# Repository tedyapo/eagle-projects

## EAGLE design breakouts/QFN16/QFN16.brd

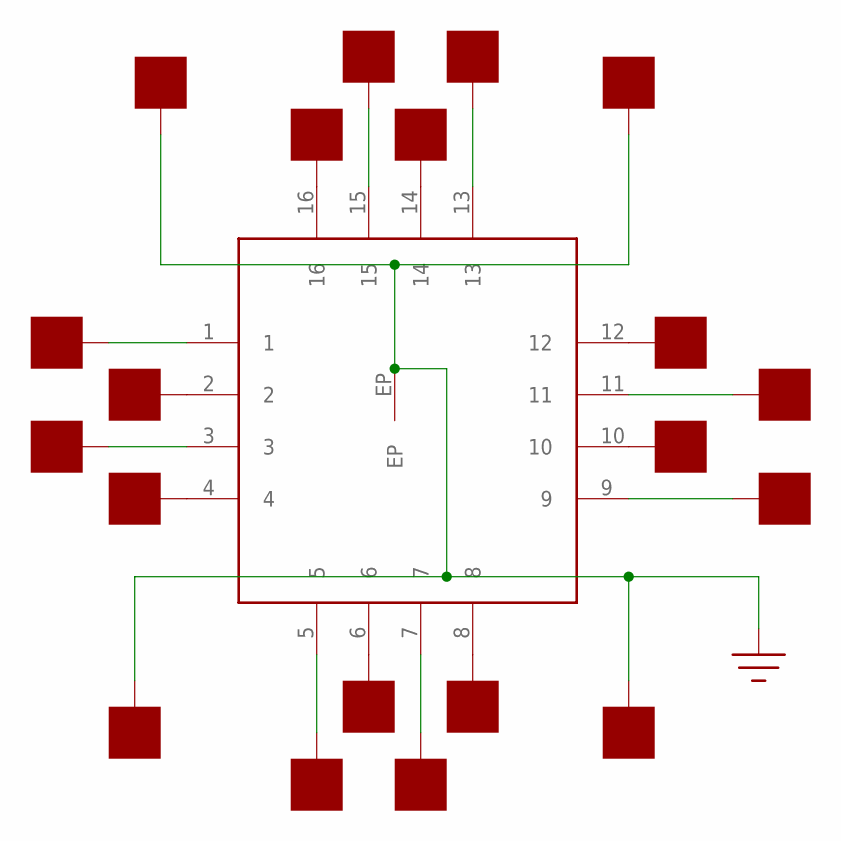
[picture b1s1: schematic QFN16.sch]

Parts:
U$1: QFN16; TQFN16-EP
U$2, U$3, U$4, U$5, U$6, U$7, U$8, U$9, U$10, U$11, U$12, U$13, U$14, U$15, U$16, U$17, U$18, U$19, U$20, U$21: PAD50MIL; PAD_50MIL

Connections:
GND: U$1.EP, U$18.P$1, U$19.P$1, U$20.P$1, U$21.P$1
unnamed: U$1.12, U$2.P$1
unnamed: U$1.10, U$4.P$1
unnamed: U$1.8, U$6.P$1
unnamed: U$1.6, U$8.P$1
unnamed: U$1.4, U$10.P$1
unnamed: U$1.2, U$12.P$1
unnamed: U$1.16, U$14.P$1
unnamed: U$1.14, U$16.P$1
unnamed: U$1.15, U$15.P$1
unnamed: U$1.13, U$17.P$1
unnamed: U$1.11, U$3.P$1
unnamed: U$1.9, U$5.P$1
unnamed: U$1.7, U$7.P$1
unnamed: U$1.5, U$9.P$1
unnamed: U$1.3, U$11.P$1
unnamed: U$1.1, U$13.P$1

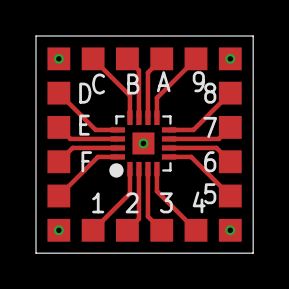
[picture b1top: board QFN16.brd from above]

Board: 2 copper layers, 12.1 x 12.1 mm, 21 parts (0 on the bottom side), 17 nets.

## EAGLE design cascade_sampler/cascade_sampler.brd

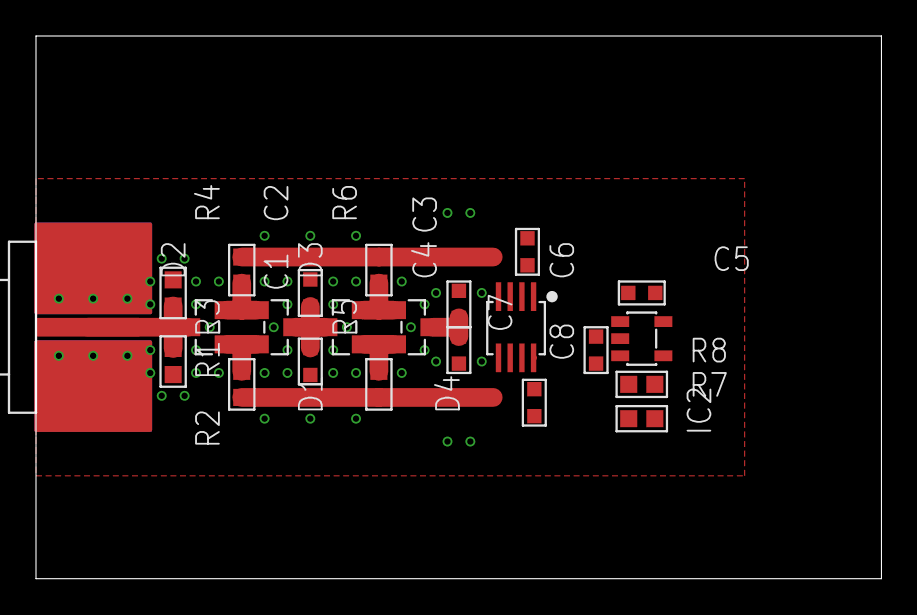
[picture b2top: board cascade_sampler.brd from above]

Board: 4 copper layers, 47.0 x 30.1 mm, 23 parts (0 on the bottom side), 14 nets.

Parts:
C1, C2, C3, C4, C5, C6, C7, C8: C0603
D1, D2, D3, D4: SOT-23
IC1: SSOP8
IC2: SOT23-5
J1: EDGE_LAUNCH_RF_CON_NARROW
R1, R2, R3, R4, R5, R6, R7, R8: R0603

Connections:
+2.5V: C5.P$2, C7.P$2, IC1.1, IC1.8, IC2.5
-2.5V: C6.P$2, C8.P$2, IC1.2, IC1.4, IC1.7, IC2.2
GND: C1.P$1, C2.P$2, C3.P$2, C4.P$1, C5.P$1, C6.P$1, C7.P$1, C8.P$1, J1.GND@1, J1.GND@2, J1.GND@3, J1.GND@4, J1.GND@5, J1.GND@6, J1.SHIELD@1, J1.SHIELD@2, R1.P$1, R2.P$2, R7.P$2
unnamed: D2.3, J1.CENTER, R1.P$2, R2.P$1
unnamed: C1.P$2, C2.P$1, D1.3, D3.3
unnamed: D1.2, D2.1, R3.P$2
unnamed: D1.1, D2.2, R4.P$1
unnamed: C3.P$1, C4.P$2, D4.3, IC2.1
unnamed: D3.1, D4.2, R5.P$2
unnamed: D3.2, D4.1, R6.P$1
unnamed: IC2.3, R7.P$1, R8.P$1
unnamed: IC2.4, R8.P$2
S+: IC1.5, R3.P$1, R5.P$1
S-: IC1.3, R4.P$2, R6.P$2

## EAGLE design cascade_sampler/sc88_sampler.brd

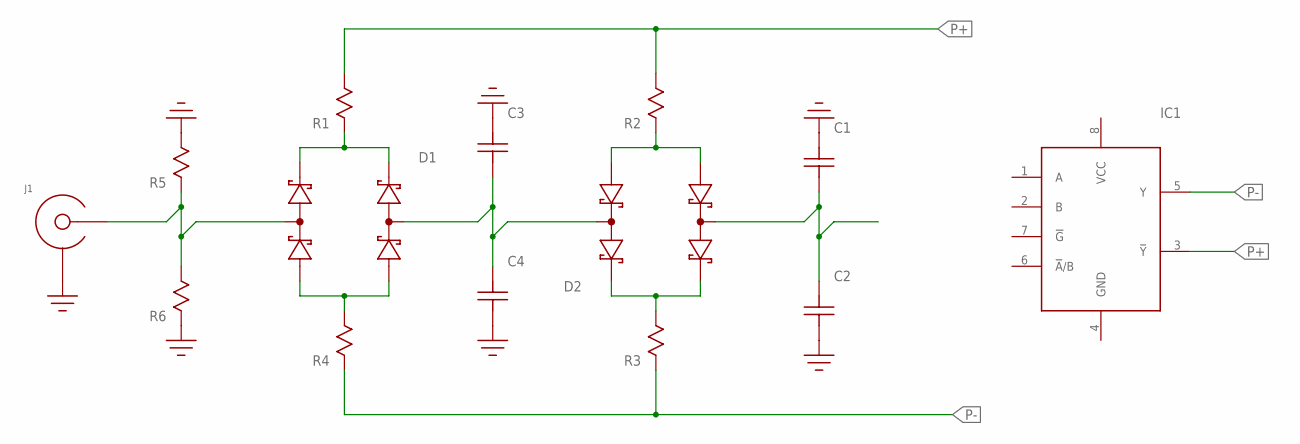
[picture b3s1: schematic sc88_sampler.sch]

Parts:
C1, C2, C3, C4: C; C0402
D1, D2: SMS3923-081; SC-88
IC1: 74LVC2G157; SSOP8
J1: EDGE_LAUNCH_JACK; EDGE_LAUNCH_RF_CON
R1, R2, R3, R4, R5, R6: R0402; 0402

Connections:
GND: C1.2, C2.1, C3.2, C4.1, J1.GND@1 (SHIELD), J1.GND@2 (SHIELD), J1.GND@3 (SHIELD), J1.GND@4 (SHIELD), J1.GND@5 (SHIELD), J1.GND@6 (SHIELD), J1.GND@7 (SHIELD), J1.GND@8 (SHIELD), J1.GND@9 (SHIELD), J1.GND@10 (SHIELD), J1.GND@11 (SHIELD), J1.GND@12 (SHIELD), J1.SHIELD@1 (SHIELD), J1.SHIELD@2 (SHIELD), R5.2, R6.1
unnamed: D1.5 (COMMON1), J1.CENTER, R5.1, R6.2
unnamed: D1.1 (ANODE0), D1.6 (ANODE1), R4.2
unnamed: D1.3 (CATHODE0), D1.4 (CATHODE1), R1.1
unnamed: C1.1, C2.2, D2.5 (COMMON1)
unnamed: D2.1 (ANODE0), D2.6 (ANODE1), R2.1
unnamed: D2.3 (CATHODE0), D2.4 (CATHODE1), R3.2
unnamed: C3.1, C4.2, D1.2 (COMMON0), D2.2 (COMMON0)
P+: IC1.3 (!Y!), R1.2, R2.2
P-: IC1.5 (Y), R3.1, R4.1

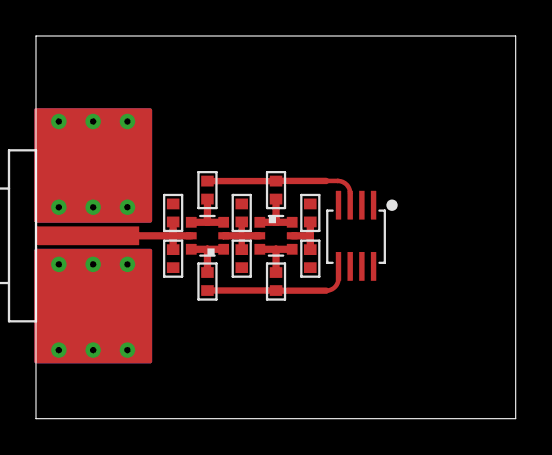
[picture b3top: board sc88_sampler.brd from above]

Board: 2 copper layers, 26.6 x 21.3 mm, 14 parts (0 on the bottom side), 10 nets.

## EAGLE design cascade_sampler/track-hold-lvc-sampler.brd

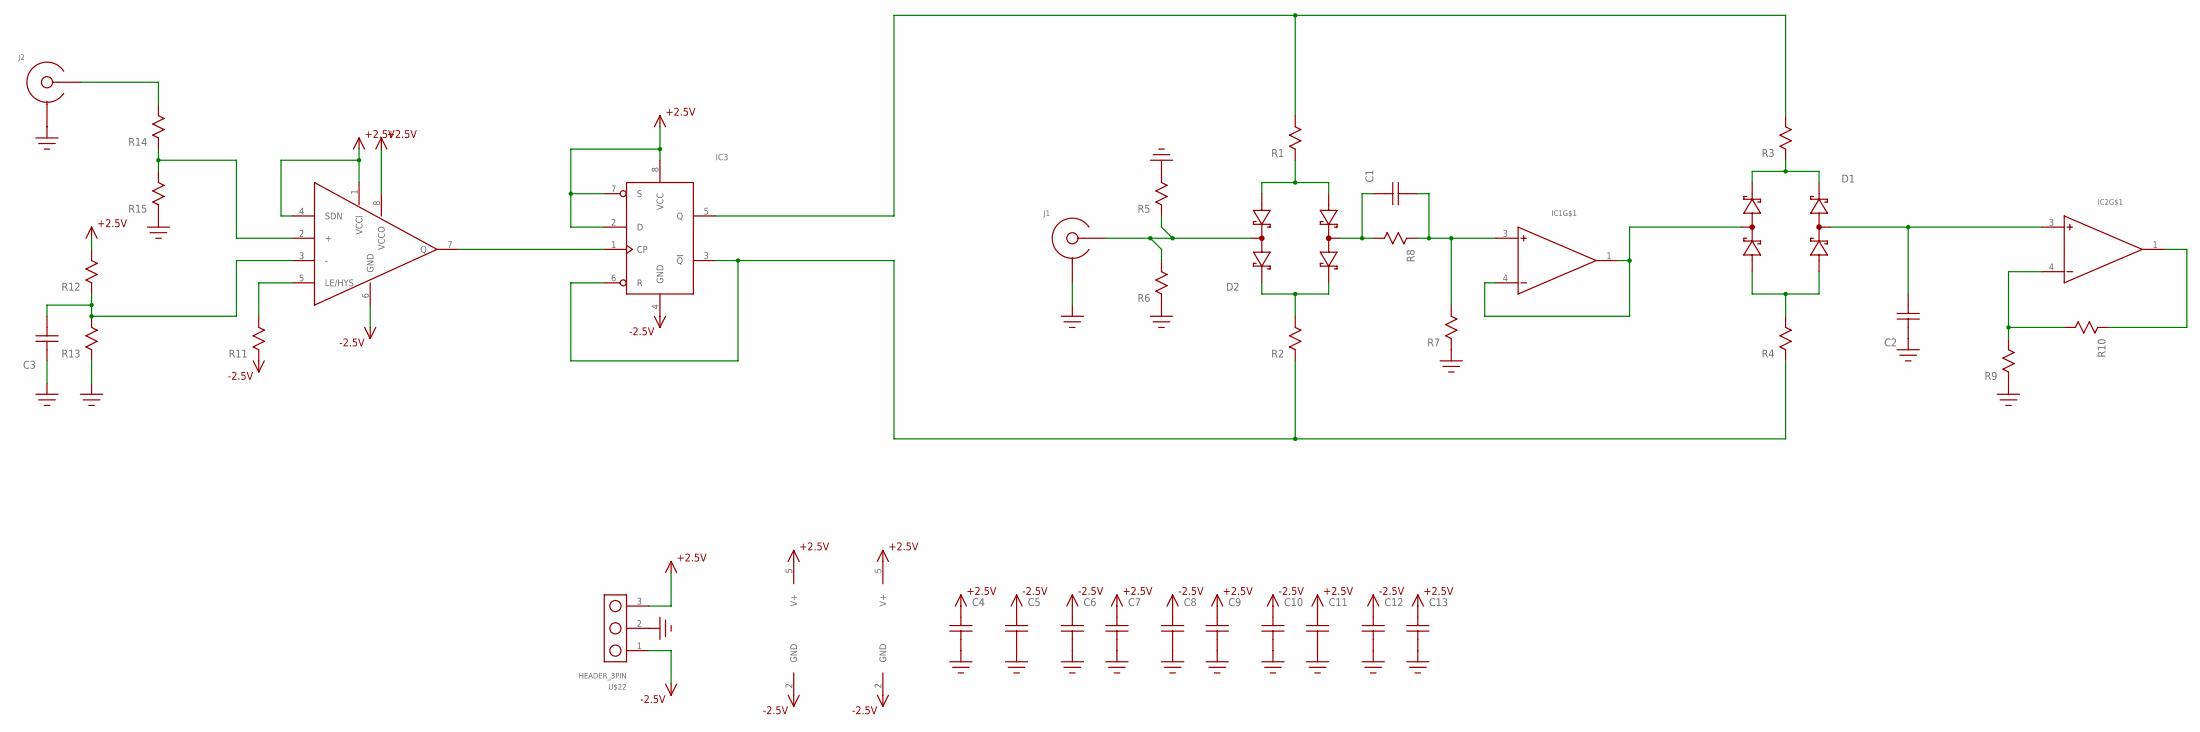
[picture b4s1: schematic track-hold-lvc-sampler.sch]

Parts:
C1, C2, C3, C6, C7, C8, C9, C10, C11, C12, C13: C0603
C4, C5: C1206; 1206
D1, D2: SMS3923-081; SC-88
IC1, IC2: ADA4000TSOT; TSOT-23
IC3: 74LVC2G74; SSOP8
IC4: ADCMP602; MSOP8
J1, J2: SMA-EDGE-LAUNCH4L-4020-TAPER-FIXED; SMA_EDGE_LAUNCH_4L_4020_TAPER_FIXED
R1, R2, R3, R4, R7, R8, R9, R10, R11, R12, R13, R14, R15: R0603
R5, R6: R0402; 0402
U$22: HEADER_3PIN

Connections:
+2.5V: C4.P$2, C7.P$2, C9.P$2, C11.P$2, C13.P$2, IC1.5 (V+), IC2.5 (V+), IC3.2 (D), IC3.7 (S), IC3.8 (VCC), IC4.1 (VCCI), IC4.4 (SDN), IC4.8 (VCCO), R12.P$2, U$22.3
-2.5V: C5.P$2, C6.P$2, C8.P$2, C10.P$2, C12.P$2, IC1.2 (GND), IC2.2 (GND), IC3.4 (GND), IC4.6 (GND), R11.P$1, U$22.1
GND: C2.P$2, C3.P$2, C4.P$1, C5.P$1, C6.P$1, C7.P$1, C8.P$1, C9.P$1, C10.P$1, C11.P$1, C12.P$1, C13.P$1, J1.BOTTOM_GND (SHIELD), J1.GND@1 (SHIELD), J1.GND@2 (SHIELD), J1.GND@3 (SHIELD), J1.GND@4 (SHIELD), J1.GND@5 (SHIELD), J1.GND@6 (SHIELD), J1.GND@7 (SHIELD), J1.GND@8 (SHIELD), J1.GND@14 (SHIELD), J1.GND@15 (SHIELD), J1.GND@16 (SHIELD), J1.GND@17 (SHIELD), J1.GND_PAD1 (SHIELD), J1.GND_PAD2 (SHIELD), J1.P$1 (SHIELD), J1.P$2 (SHIELD), J2.BOTTOM_GND (SHIELD), J2.GND@1 (SHIELD), J2.GND@2 (SHIELD), J2.GND@3 (SHIELD), J2.GND@4 (SHIELD), J2.GND@5 (SHIELD), J2.GND@6 (SHIELD), J2.GND@7 (SHIELD), J2.GND@8 (SHIELD), J2.GND@14 (SHIELD), J2.GND@15 (SHIELD), J2.GND@16 (SHIELD), J2.GND@17 (SHIELD), J2.GND_PAD1 (SHIELD), J2.GND_PAD2 (SHIELD), J2.P$1 (SHIELD), J2.P$2 (SHIELD), R5.2, R6.1, R7.P$1, R9.P$1, R13.P$1, R15.P$1, U$22.2
unnamed: D2.2 (COMMON0), J1.CENTER@1 (CENTER), J1.P$3 (CENTER), R5.1, R6.2
unnamed: D2.1 (ANODE0), D2.6 (ANODE1), R1.P$1
unnamed: D2.3 (CATHODE0), D2.4 (CATHODE1), R2.P$2
unnamed: D1.3 (CATHODE0), D1.4 (CATHODE1), R3.P$1
unnamed: D1.1 (ANODE0), D1.6 (ANODE1), R4.P$2
unnamed: D1.5 (COMMON1), IC1.1 (OUT), IC1.4 (-)
unnamed: C1.P$2, D2.5 (COMMON1), R8.P$2
unnamed: C1.P$1, IC1.3 (+), R7.P$2, R8.P$1
unnamed: IC3.3 (!Q!), IC3.6 (R), R2.P$1, R4.P$1
unnamed: IC3.1 (CP), IC4.7 (Q)
unnamed: C2.P$1, D1.2 (COMMON0), IC2.3 (+)
unnamed: IC2.4 (-), R9.P$2, R10.P$2
unnamed: IC2.1 (OUT), R10.P$1
unnamed: IC4.5 (LE/HYS), R11.P$2
unnamed: IC3.5 (Q), R1.P$2, R3.P$2
unnamed: C3.P$1, IC4.3 (-), R12.P$1, R13.P$2
unnamed: J2.CENTER@1 (CENTER), J2.P$3 (CENTER), R14.P$2
unnamed: IC4.2 (+), R14.P$1, R15.P$2

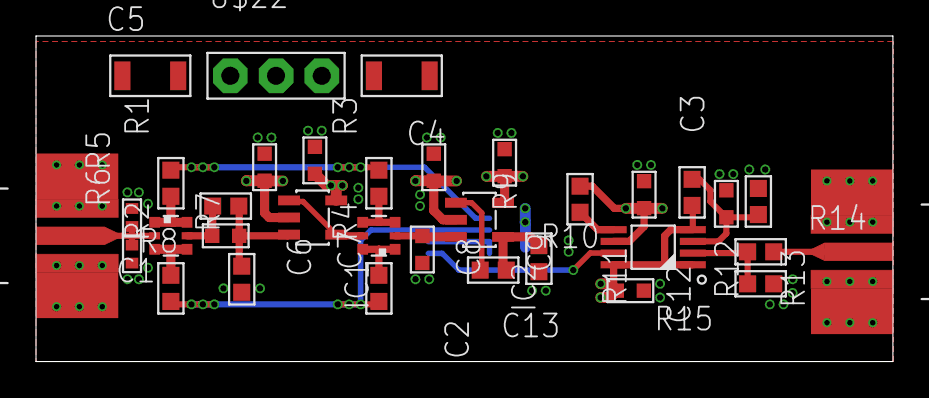
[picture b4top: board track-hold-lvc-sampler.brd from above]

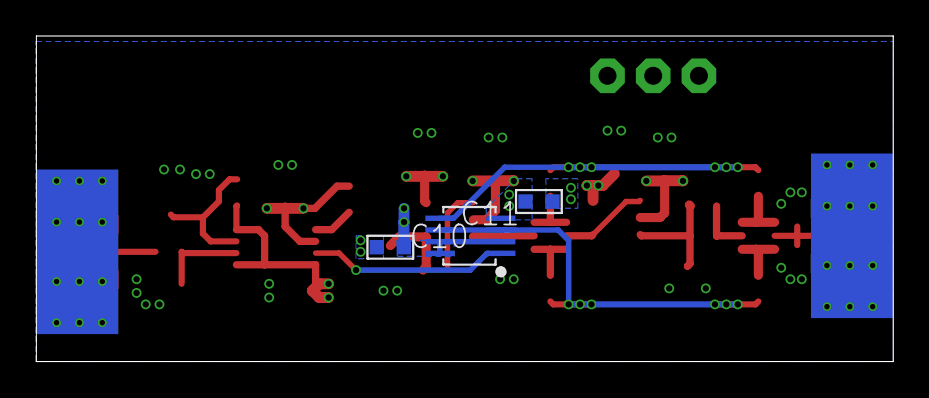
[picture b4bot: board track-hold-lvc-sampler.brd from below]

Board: 4 copper layers, 47.6 x 18.1 mm, 37 parts (3 on the bottom side), 21 nets.

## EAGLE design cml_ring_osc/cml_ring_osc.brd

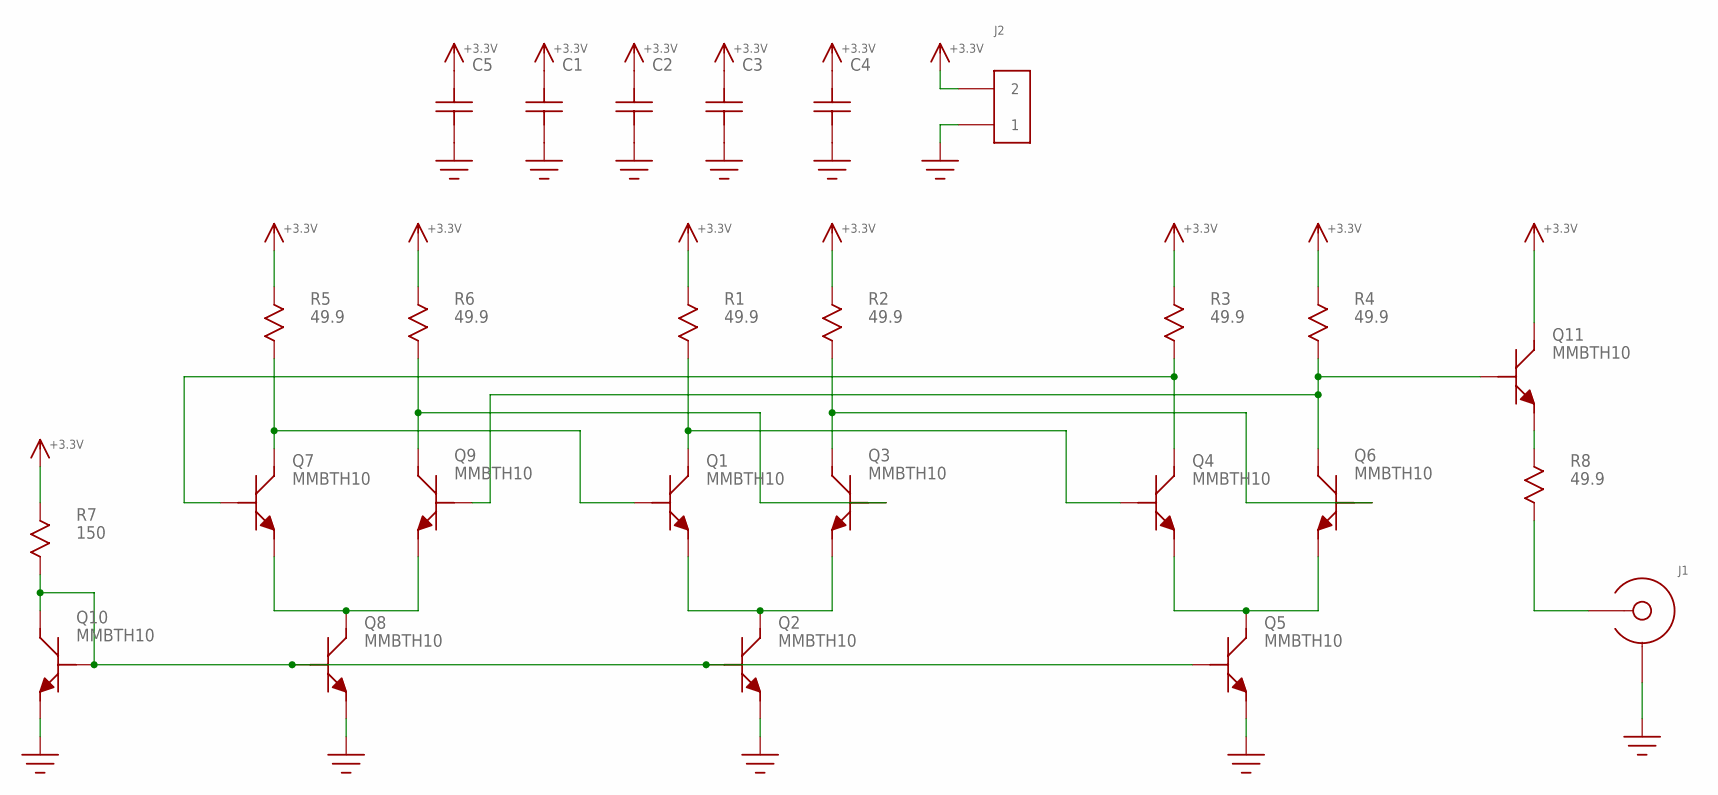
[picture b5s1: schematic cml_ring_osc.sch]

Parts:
C1, C2, C3: C0603
C4, C5: C0805; 0805
J1: EDGE_LAUNCH_JACK; EDGE_LAUNCH_RF_CON
J2: HEADER_2PIN
Q1, Q2, Q3, Q4, Q5, Q6, Q7, Q8, Q9, Q10, Q11: MMBTH10; SOT-23
R1, R2, R3, R4, R5, R6: 49.9; R0603
R7: 150; R0603
R8: 49.9; R0805

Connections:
+3.3V: C1.P$2, C2.P$2, C3.P$2, C4.P$2, C5.P$2, J2.2, Q11.3 (C), R1.P$1, R2.P$1, R3.P$1, R4.P$1, R5.P$1, R6.P$1, R7.P$1
GND: C1.P$1, C2.P$1, C3.P$1, C4.P$1, C5.P$1, J1.GND@1 (SHIELD), J1.GND@2 (SHIELD), J1.GND@3 (SHIELD), J1.GND@4 (SHIELD), J1.GND@5 (SHIELD), J1.GND@6 (SHIELD), J1.GND@7 (SHIELD), J1.GND@8 (SHIELD), J1.GND@9 (SHIELD), J1.GND@10 (SHIELD), J1.GND@11 (SHIELD), J1.GND@12 (SHIELD), J1.SHIELD@1 (SHIELD), J1.SHIELD@2 (SHIELD), J2.1, Q2.2 (E), Q5.2 (E), Q8.2 (E), Q10.2 (E)
unnamed: Q1.3 (C), Q4.1 (B), R1.P$2
unnamed: Q4.3 (C), Q7.1 (B), R3.P$2
unnamed: Q3.3 (C), Q6.1 (B), R2.P$2
unnamed: Q1.2 (E), Q2.3 (C), Q3.2 (E)
unnamed: Q6.3 (C), Q9.1 (B), Q11.1 (B), R4.P$2
unnamed: Q4.2 (E), Q5.3 (C), Q6.2 (E)
unnamed: Q1.1 (B), Q7.3 (C), R5.P$2
unnamed: Q3.1 (B), Q9.3 (C), R6.P$2
unnamed: Q7.2 (E), Q8.3 (C), Q9.2 (E)
unnamed: Q2.1 (B), Q5.1 (B), Q8.1 (B), Q10.1 (B), Q10.3 (C), R7.P$2
unnamed: Q11.2 (E), R8.P$1
unnamed: J1.CENTER, R8.P$2

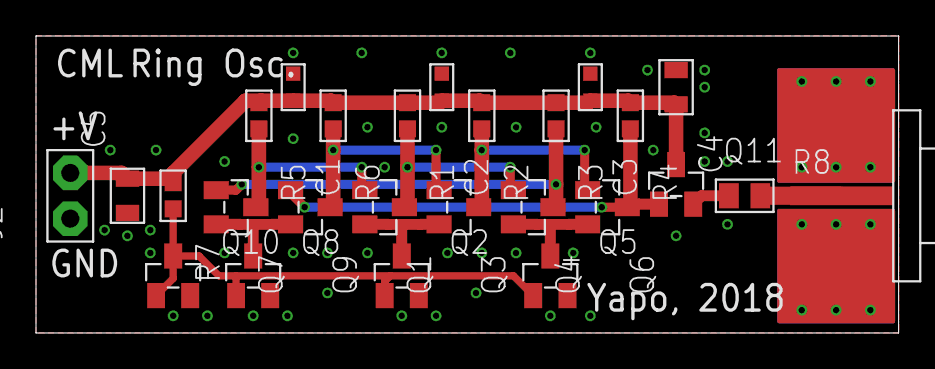
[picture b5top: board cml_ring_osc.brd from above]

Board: 2 copper layers, 47.9 x 16.5 mm, 26 parts (0 on the bottom side), 14 nets.

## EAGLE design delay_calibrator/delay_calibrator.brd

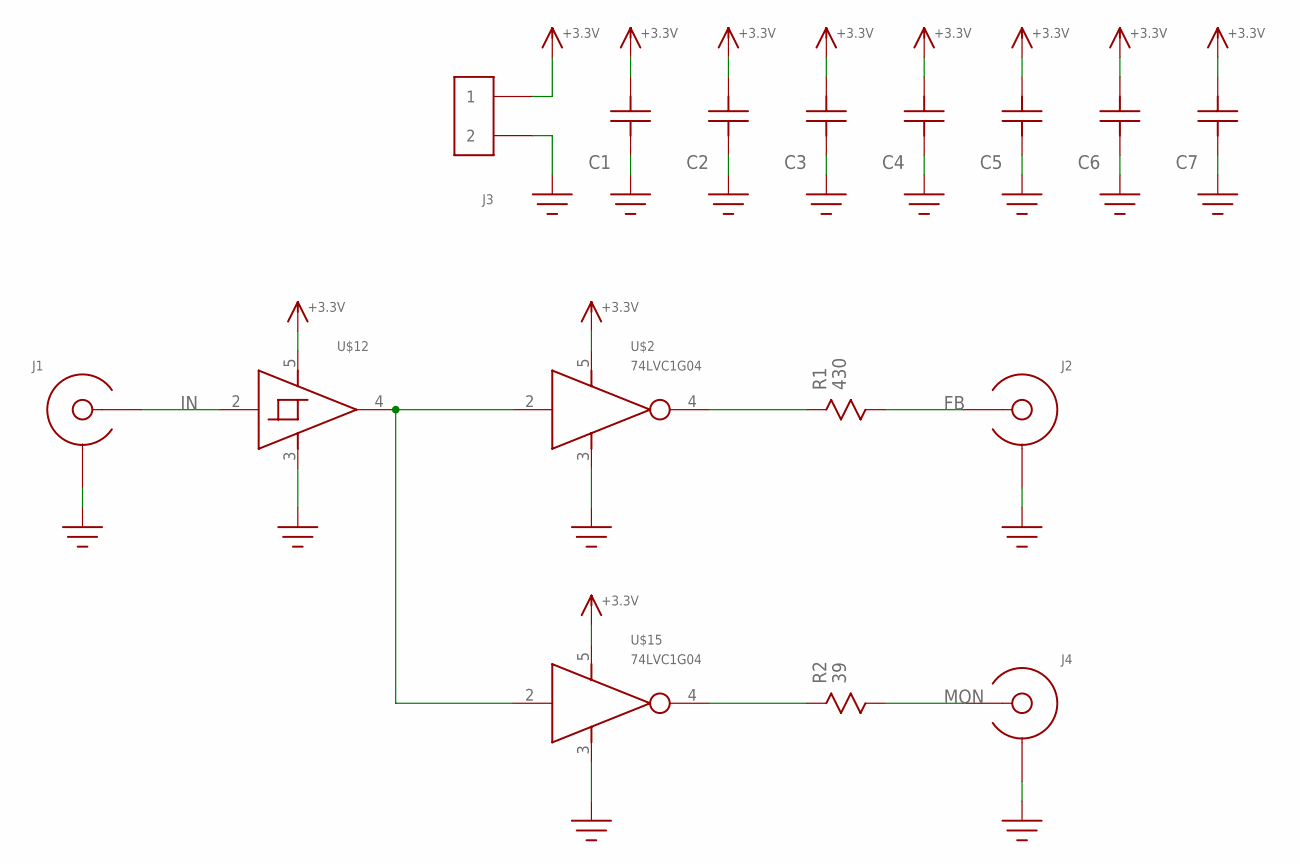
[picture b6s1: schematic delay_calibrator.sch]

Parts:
C1: C1206; 1206
C2, C3, C4, C5, C6, C7: C0603
J1, J2, J4: EDGE_LAUNCH_JACK; EDGE_LAUNCH_RF_CON
J3: HEADER_2PIN
R1: 430; R0603
R2: 39; R0603
U$2, U$15: 74LVC1G04; SOT23-5
U$12: 74LVC1G17; SOT23-5

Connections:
+3.3V: C1.P$1, C2.P$1, C3.P$1, C4.P$1, C5.P$1, C6.P$1, C7.P$1, J3.1, U$2.5 (VCC), U$12.5 (VCC), U$15.5 (VCC)
FB: J2.CENTER, R1.P$2
GND: C1.P$2, C2.P$2, C3.P$2, C4.P$2, C5.P$2, C6.P$2, C7.P$2, J1.GND@1 (SHIELD), J1.GND@2 (SHIELD), J1.GND@3 (SHIELD), J1.GND@4 (SHIELD), J1.GND@5 (SHIELD), J1.GND@6 (SHIELD), J1.GND@7 (SHIELD), J1.GND@8 (SHIELD), J1.GND@9 (SHIELD), J1.GND@10 (SHIELD), J1.GND@11 (SHIELD), J1.GND@12 (SHIELD), J1.SHIELD@1 (SHIELD), J1.SHIELD@2 (SHIELD), J2.GND@1 (SHIELD), J2.GND@2 (SHIELD), J2.GND@3 (SHIELD), J2.GND@4 (SHIELD), J2.GND@5 (SHIELD), J2.GND@6 (SHIELD), J2.GND@7 (SHIELD), J2.GND@8 (SHIELD), J2.GND@9 (SHIELD), J2.GND@10 (SHIELD), J2.GND@11 (SHIELD), J2.GND@12 (SHIELD), J2.SHIELD@1 (SHIELD), J2.SHIELD@2 (SHIELD), J3.2, J4.GND@1 (SHIELD), J4.GND@2 (SHIELD), J4.GND@3 (SHIELD), J4.GND@4 (SHIELD), J4.GND@5 (SHIELD), J4.GND@6 (SHIELD), J4.GND@7 (SHIELD), J4.GND@8 (SHIELD), J4.GND@9 (SHIELD), J4.GND@10 (SHIELD), J4.GND@11 (SHIELD), J4.GND@12 (SHIELD), J4.SHIELD@1 (SHIELD), J4.SHIELD@2 (SHIELD), U$2.3 (GND), U$12.3 (GND), U$15.3 (GND)
IN: J1.CENTER, U$12.2 (IN)
MON: J4.CENTER, R2.P$2
unnamed: R2.P$1, U$15.4 (OUT)
unnamed: R1.P$1, U$2.4 (OUT)
unnamed: U$2.2 (IN), U$12.4 (OUT), U$15.2 (IN)

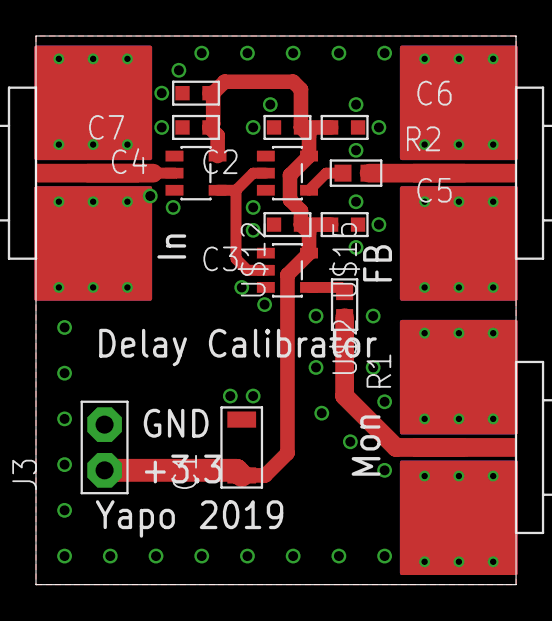
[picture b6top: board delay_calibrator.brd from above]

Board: 2 copper layers, 26.7 x 30.5 mm, 16 parts (0 on the bottom side), 8 nets.

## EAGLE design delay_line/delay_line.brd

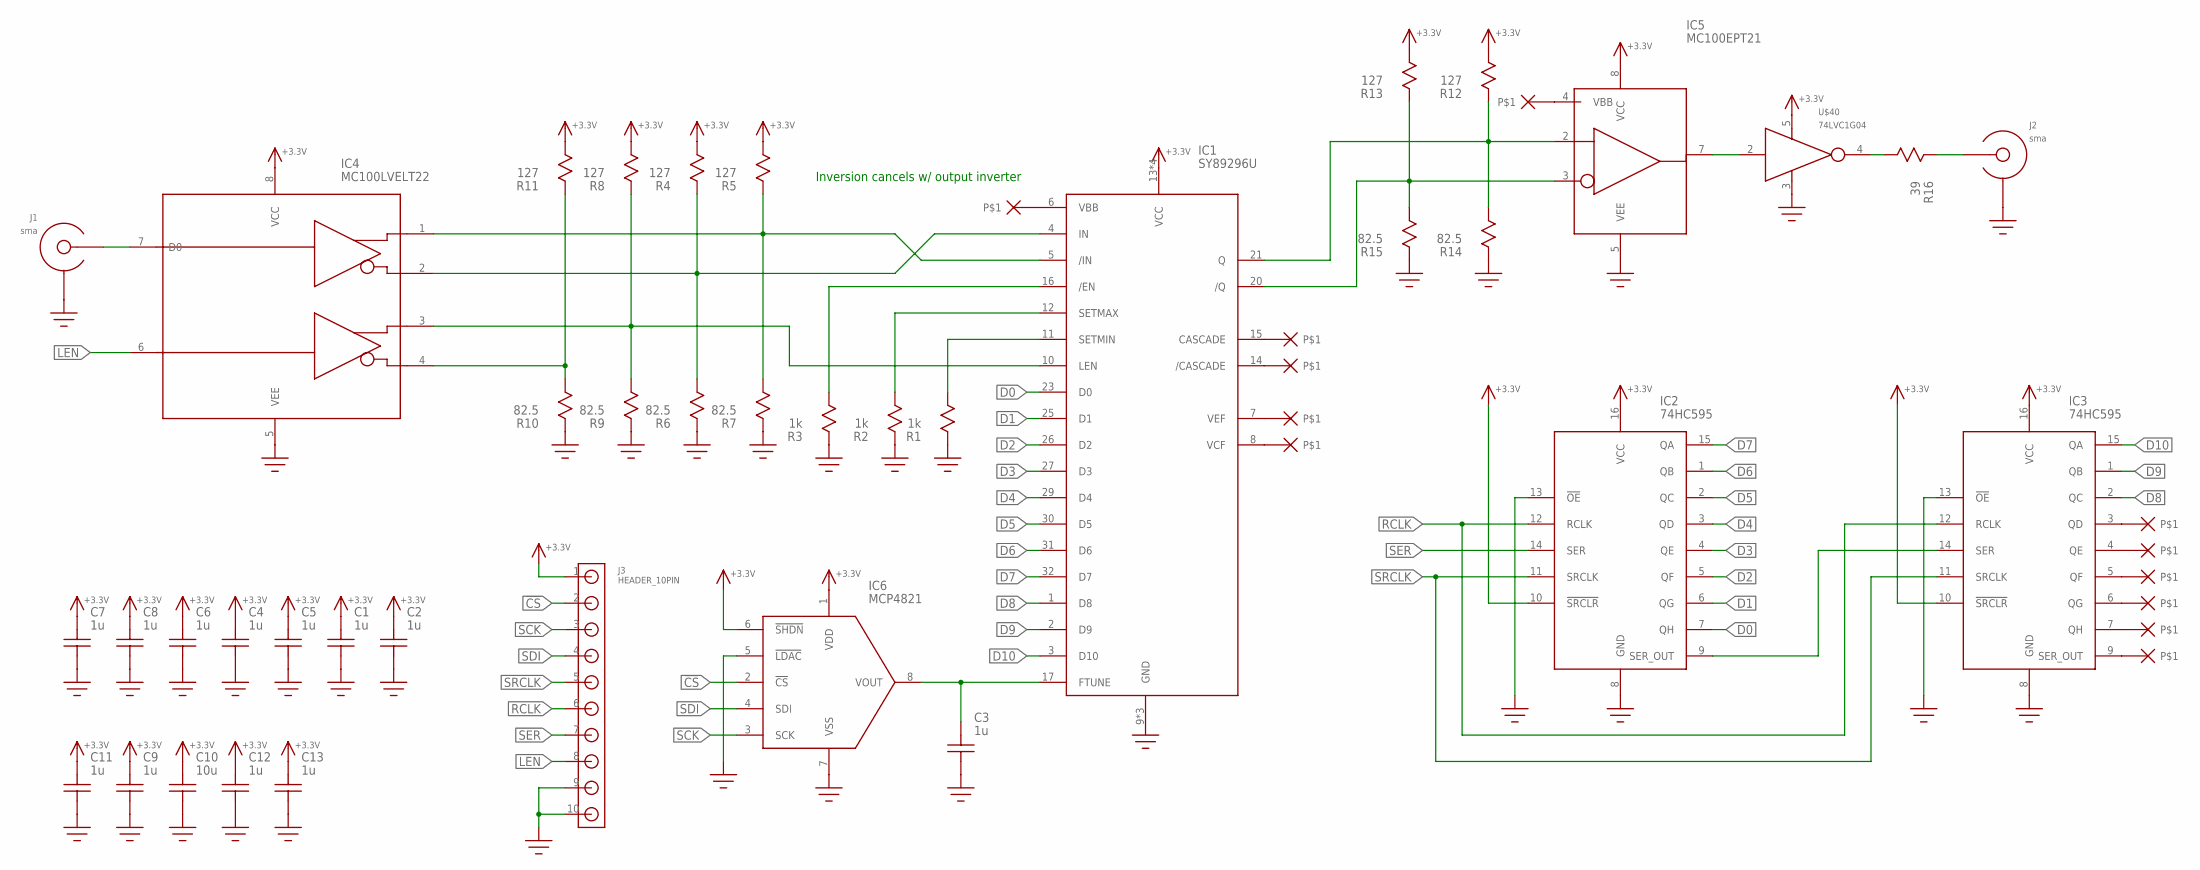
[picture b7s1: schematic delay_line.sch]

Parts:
C1, C2, C3, C4, C5, C6, C7, C8, C12: 1u; C0603
C9, C11, C13: 1u; 0805
C10: 10u; 1206
IC1: SY89296U; TQFP32_7X7
IC2, IC3: 74HC595; SOIC-16
IC4: MC100LVELT22; SOIC8
IC5: MC100EPT21; SOIC8
IC6: MCP4821; SOIC8
J1, J2: sma; EDGE_LAUNCH_RF_CON
J3: HEADER_10PIN
R1, R2, R3: 1k; R0603
R4, R5, R8, R11, R12, R13: 127; R0603
R6, R7, R9, R10, R14, R15: 82.5; R0603
R16: 39; R0603
U$40: 74LVC1G04; SOT23-5

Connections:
!CS!: IC6.2 (!CS!), J3.2
+3.3V: C1.P$2, C2.P$2, C4.P$2, C5.P$2, C6.P$2, C7.P$2, C8.P$2, C9.P$2, C10.P$2, C11.P$2, C12.P$2, C13.P$2, IC1.13 (VCC), IC1.18 (VCC), IC1.19 (VCC), IC1.22 (VCC), IC2.10 (!SRCLR!), IC2.16 (VCC), IC3.10 (!SRCLR!), IC3.16 (VCC), IC4.8 (VCC), IC5.8 (VCC), IC6.1 (VDD), IC6.6 (!SHDN!), J3.1, R4.P$2, R5.P$2, R8.P$2, R11.P$2, R12.P$2, R13.P$2, U$40.5 (VCC)
D0: IC1.23 (D0), IC2.7 (QH)
D1: IC1.25 (D1), IC2.6 (QG)
D2: IC1.26 (D2), IC2.5 (QF)
D3: IC1.27 (D3), IC2.4 (QE)
D4: IC1.29 (D4), IC2.3 (QD)
D5: IC1.30 (D5), IC2.2 (QC)
D6: IC1.31 (D6), IC2.1 (QB)
D7: IC1.32 (D7), IC2.15 (QA)
D8: IC1.1 (D8), IC3.2 (QC)
D9: IC1.2 (D9), IC3.1 (QB)
D10: IC1.3 (D10), IC3.15 (QA)
GND: C1.P$1, C2.P$1, C3.P$1, C4.P$1, C5.P$1, C6.P$1, C7.P$1, C8.P$1, C9.P$1, C10.P$1, C11.P$1, C12.P$1, C13.P$1, IC1.9 (GND), IC1.24 (GND), IC1.28 (GND), IC2.8 (GND), IC2.13 (!OE!), IC3.8 (GND), IC3.13 (!OE!), IC4.5 (VEE), IC5.5 (VEE), IC6.5 (!LDAC!), IC6.7 (VSS), J1.GND@1 (SHIELD), J1.GND@2 (SHIELD), J1.GND@3 (SHIELD), J1.GND@4 (SHIELD), J1.GND@5 (SHIELD), J1.GND@6 (SHIELD), J1.GND@7 (SHIELD), J1.GND@8 (SHIELD), J1.GND@9 (SHIELD), J1.GND@10 (SHIELD), J1.GND@11 (SHIELD), J1.GND@12 (SHIELD), J1.SHIELD@1 (SHIELD), J1.SHIELD@2 (SHIELD), J2.GND@1 (SHIELD), J2.GND@2 (SHIELD), J2.GND@3 (SHIELD), J2.GND@4 (SHIELD), J2.GND@5 (SHIELD), J2.GND@6 (SHIELD), J2.GND@7 (SHIELD), J2.GND@8 (SHIELD), J2.GND@9 (SHIELD), J2.GND@10 (SHIELD), J2.GND@11 (SHIELD), J2.GND@12 (SHIELD), J2.SHIELD@1 (SHIELD), J2.SHIELD@2 (SHIELD), J3.9, J3.10, R1.P$1, R2.P$1, R3.P$1, R6.P$1, R7.P$1, R9.P$1, R10.P$1, R14.P$1, R15.P$1, U$40.3 (GND)
IN_N: IC1.5 (/IN), IC4.1 (Q0), R5.P$1, R7.P$2
IN_P: IC1.4 (IN), IC4.2 (!Q0!), R4.P$1, R6.P$2
LEN: IC4.6 (D1), J3.8
unnamed: IC2.9 (SER_OUT), IC3.14 (SER)
unnamed: IC1.11 (SETMIN), R1.P$2
unnamed: IC1.12 (SETMAX), R2.P$2
unnamed: IC1.16 (/EN), R3.P$2
unnamed: IC1.10 (LEN), IC4.3 (Q1), R8.P$1, R9.P$2
unnamed: IC4.4 (!Q1!), R10.P$2, R11.P$1
unnamed: IC5.7 (Q), U$40.2 (IN)
unnamed: IC4.7 (D0), J1.CENTER
unnamed: R16.P$2, U$40.4 (OUT)
unnamed: J2.CENTER, R16.P$1
unnamed: C3.P$2, IC1.17 (FTUNE), IC6.8 (VOUT)
Q_N: IC1.20 (/Q), IC5.3 (!D!), R13.P$1, R15.P$2
Q_P: IC1.21 (Q), IC5.2 (D), R12.P$1, R14.P$2
RCLK: IC2.12 (RCLK), IC3.12 (RCLK), J3.6
SCK: IC6.3 (SCK), J3.3
SDI: IC6.4 (SDI), J3.4
SER: IC2.14 (SER), J3.7
SRCLK: IC2.11 (SRCLK), IC3.11 (SRCLK), J3.5

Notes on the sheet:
Inversion cancels w/ output inverter

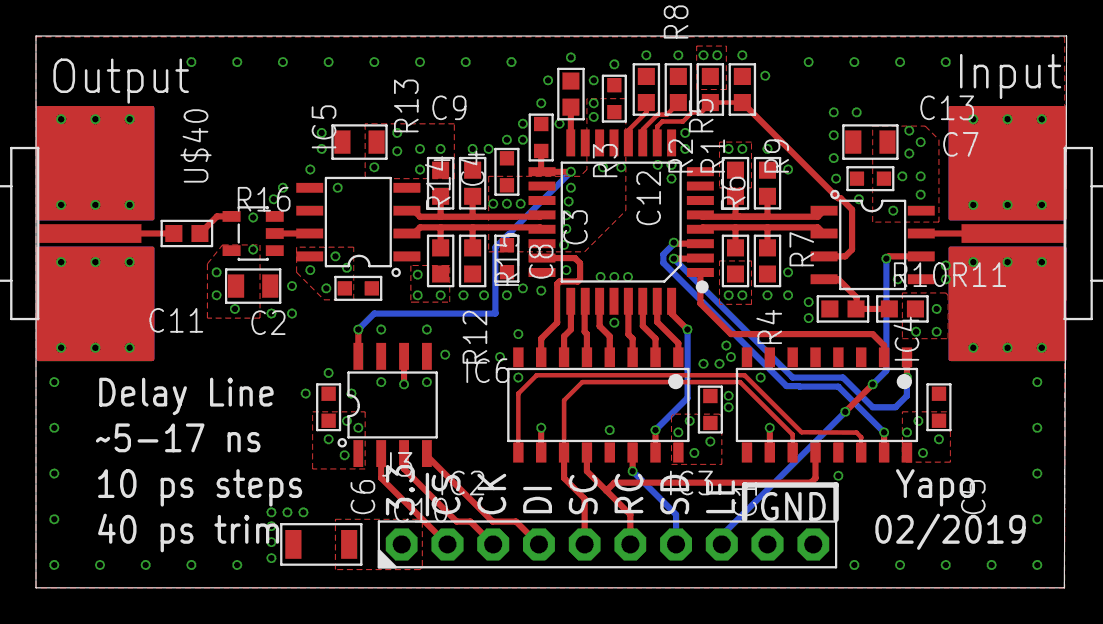
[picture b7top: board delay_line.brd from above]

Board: 4 copper layers, 57.3 x 30.7 mm, 39 parts (0 on the bottom side), 35 nets.
